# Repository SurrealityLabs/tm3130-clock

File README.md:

# tm3130-clock
A small clock display based on the TM3130 display IC

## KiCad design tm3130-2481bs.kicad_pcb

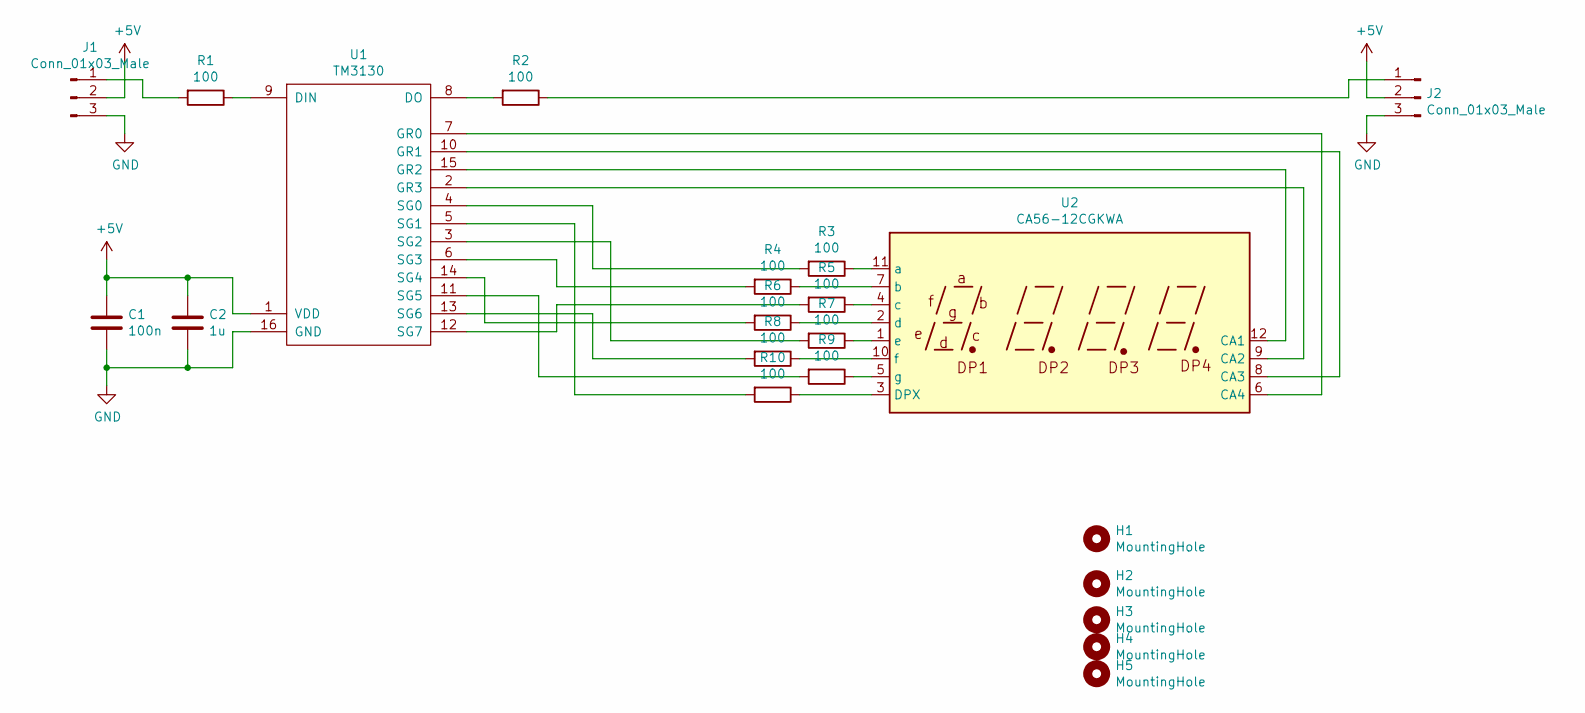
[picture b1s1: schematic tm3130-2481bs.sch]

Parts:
C1: 100n; C_0603_1608Metric; LCSC C14663
C2: 1u; C_0603_1608Metric; LCSC C15849
H1, H2: MountingHole; MountingHole_3.2mm_M3
H3, H4, H5: MountingHole; tooling-hole
J1, J2: Conn_01x03_Male; JST_PH_S3B-PH-K_1x03_P2.00mm_Horizontal; LCSC C225208
R1, R2, R3, R4, R5, R6, R7, R8, R9, R10: 100; R_0603; LCSC C22775
U1: TM3130; SOIC-16_3.9x9.9mm_Pitch1.27mm; LCSC C94298
U2: CA56-12CGKWA; 2481BS

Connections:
+5V: C1.1, C2.1, J1.2, J2.2, U1.1 (VDD)
GND: C1.2, C2.2, J1.3, J2.3, U1.16 (GND)
unnamed: J1.1, R1.2
unnamed: J2.1, R2.1
unnamed: R1.1, U1.9 (DIN)
unnamed: R2.2, U1.8 (DO)
unnamed: R3.1, U2.11 (a)
unnamed: R3.2, U1.4 (SG0)
unnamed: R4.1, U2.7 (b)
unnamed: R4.2, U1.6 (SG3)
unnamed: R5.1, U2.4 (c)
unnamed: R5.2, U1.12 (SG7)
unnamed: R6.1, U2.2 (d)
unnamed: R6.2, U1.14 (SG4)
unnamed: R7.1, U2.1 (e)
unnamed: R7.2, U1.3 (SG2)
unnamed: R8.1, U2.10 (f)
unnamed: R8.2, U1.13 (SG6)
unnamed: R9.1, U2.5 (g)
unnamed: R9.2, U1.11 (SG5)
unnamed: R10.1, U2.3 (DPX)
unnamed: R10.2, U1.5 (SG1)
unnamed: U1.2 (GR3), U2.9 (CA2)
unnamed: U1.7 (GR0), U2.6 (CA4)
unnamed: U1.10 (GR1), U2.8 (CA3)
unnamed: U1.15 (GR2), U2.12 (CA1)

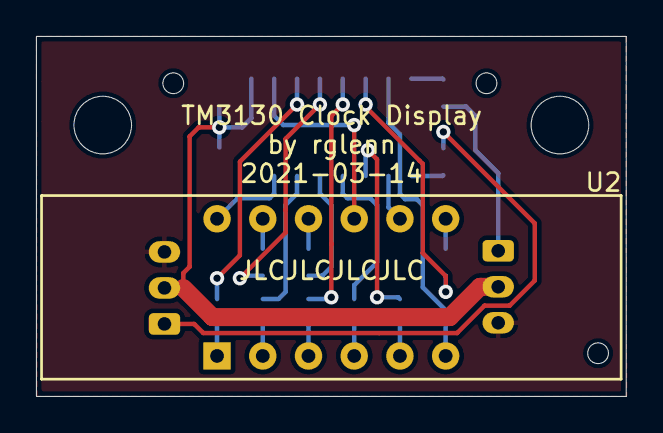
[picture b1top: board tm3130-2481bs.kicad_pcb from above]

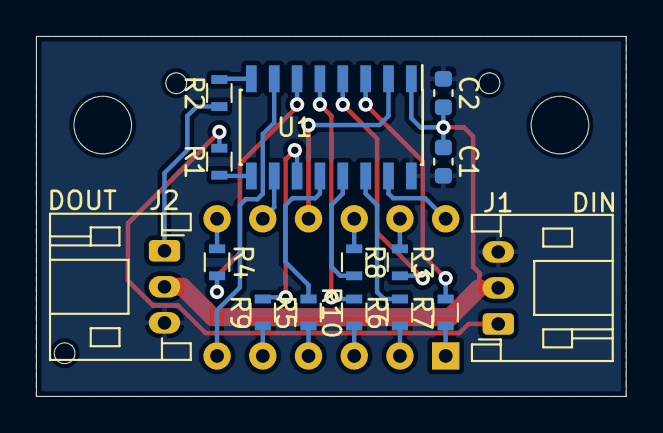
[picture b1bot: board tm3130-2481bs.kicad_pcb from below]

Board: 2 copper layers, 32.8 x 20.0 mm, 21 parts (15 on the bottom side), 26 nets.

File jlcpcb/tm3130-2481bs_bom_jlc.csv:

"Comment","Designator","Footprint","LCSC Part #"
"100n","C1","C_0603_1608Metric","C14663"
"1u","C2","C_0603_1608Metric","C15849"
"Conn_01x03_Male","J1,J2","JST_PH_S3B-PH-K_1x03_P2.00mm_Horizontal","C225208"
"100","R1,R2,R3,R4,R5,R6,R7,R8,R9,R10","R_0603","C22775"
"TM3130","U1","SOIC-16_3.9x9.9mm_Pitch1.27mm","C94298"

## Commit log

2021-03-15 Adding PCB
2021-03-28 Adding manufacturing data
